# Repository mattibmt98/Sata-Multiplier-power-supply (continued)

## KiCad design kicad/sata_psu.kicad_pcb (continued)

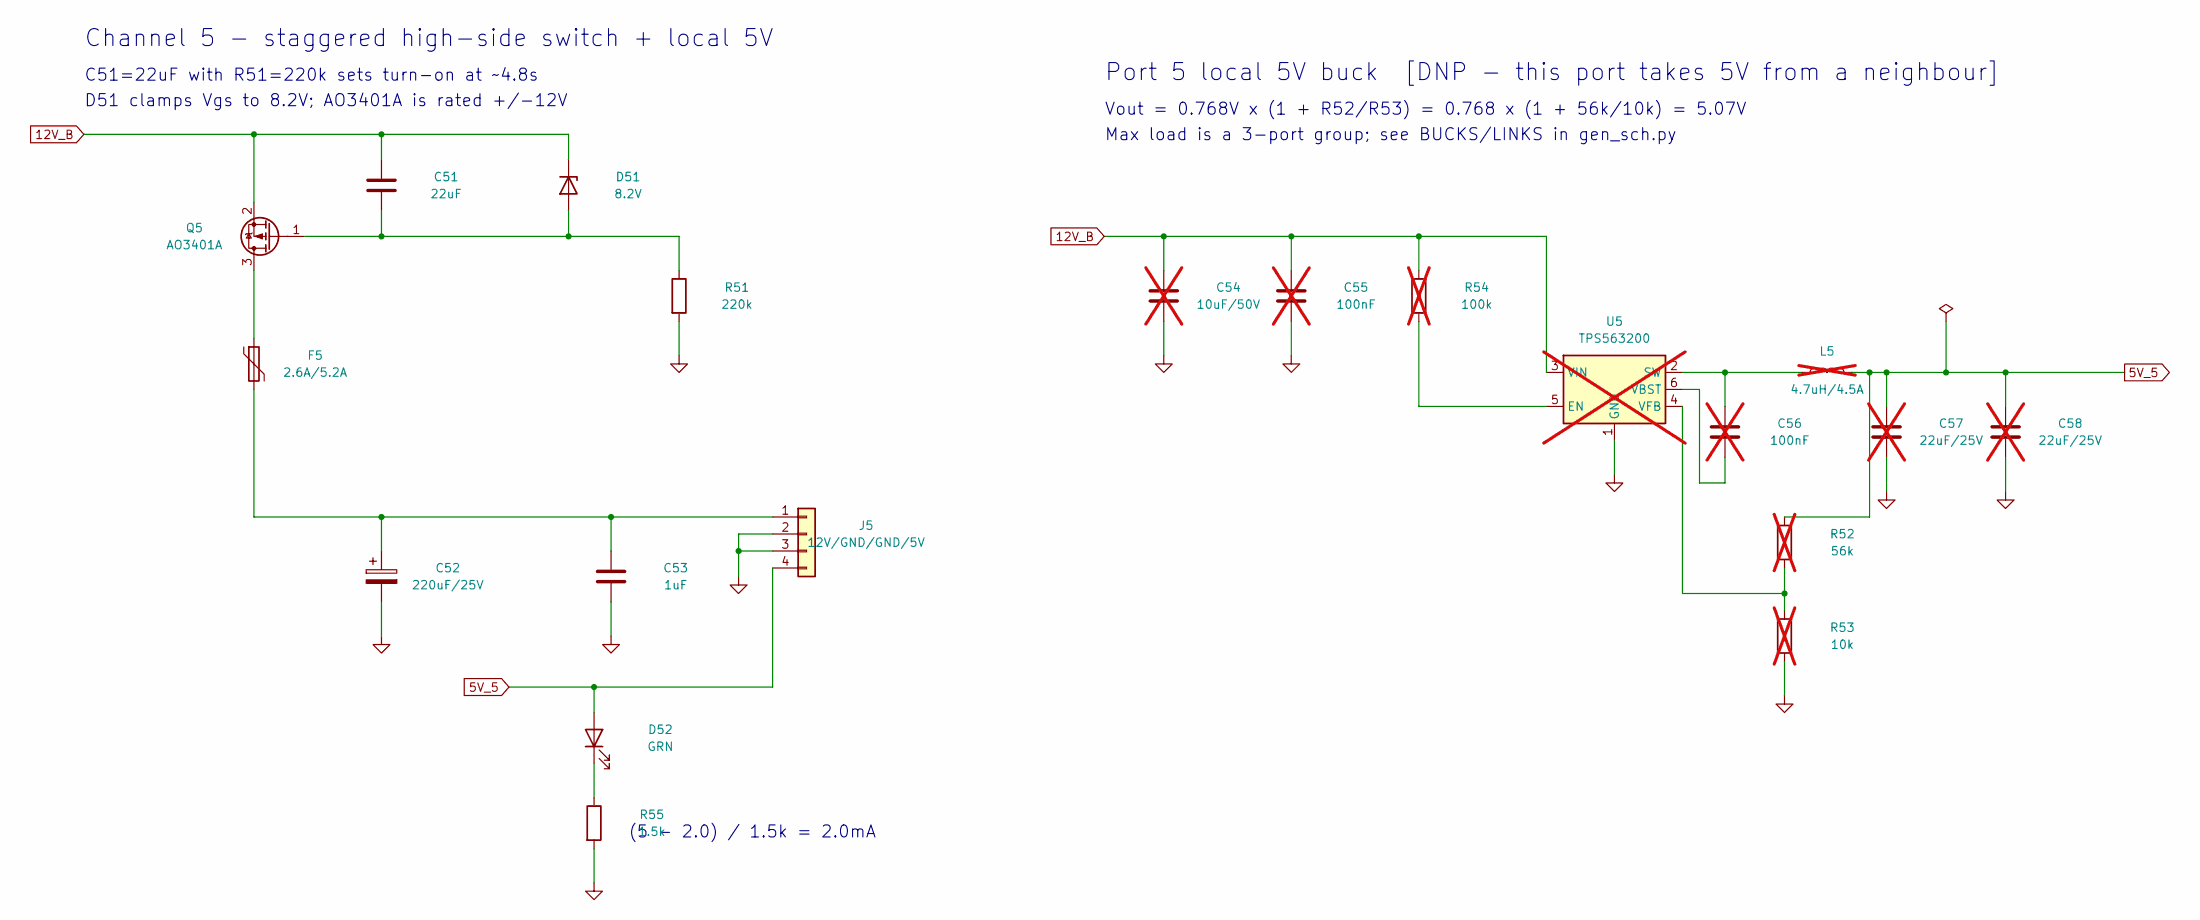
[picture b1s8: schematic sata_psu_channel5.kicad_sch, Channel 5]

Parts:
C51: 22uF; C_1206_3216Metric; MPN CL31A226KAHNNNE; DigiKey 1276-3047-1-ND
C52: 220uF/25V; CP_Radial_D8.0mm_P3.50mm; MPN UVZ1E221MPD; DigiKey 493-1302-ND
C53: 1uF; C_0603_1608Metric; MPN CL10A105KB8NNNC; DigiKey 1276-1860-1-ND
C54: 10uF/50V; C_1206_3216Metric; MPN CL31A106KBHNNNE; DigiKey 1276-2876-1-ND; not fitted
C55, C56: 100nF; C_0603_1608Metric; MPN CL10B104KB8NNNC; DigiKey 1276-1000-1-ND; not fitted
C57, C58: 22uF/25V; C_1206_3216Metric; MPN CL31A226KAHNNNE; DigiKey 1276-3047-1-ND; not fitted
D51: 8.2V; D_SOD-123; MPN MMSZ5237B-7-F; DigiKey MMSZ5237B-FDICT-ND
D52: GRN; LED_0603_1608Metric
F5: 2.6A/5.2A; Fuse_1812_4532Metric; MPN 1812L260/16MR; DigiKey F10827CT-ND
J5: 12V/GND/GND/5V; PinHeader_1x04_P2.54mm_Vertical; MPN PRPC004SAAN-RC; DigiKey S1011EC-04-ND
L5: 4.7uH/4.5A; L_Bourns_SRN6045TA; MPN SRN6045TA-4R7M; DigiKey SRN6045TA-4R7MTR-ND; not fitted
Q5: AO3401A; SOT-23; MPN AO3401A; DigiKey 785-1001-1-ND
R51: 220k; R_0603_1608Metric; MPN RC0603FR-07220KL; DigiKey 311-220KHRCT-ND
R52: 56k; R_0603_1608Metric; MPN RC0603FR-0756KL; DigiKey 311-56KHRCT-ND; not fitted
R53: 10k; R_0603_1608Metric; MPN RC0603FR-0710KL; DigiKey 311-10.0KHRCT-ND; not fitted
R54: 100k; R_0603_1608Metric; MPN RC0603FR-07100KL; DigiKey 311-100KHRCT-ND; not fitted
R55: 1.5k; R_0603_1608Metric
U5: TPS563200; SOT-23-6; MPN TPS563200DDCR; DigiKey 296-43663-1-ND; not fitted

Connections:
5V_5: C57.1, C58.1, D52.2 (A), J5.4, L5.2, R52.1; also elsewhere on the board
12V_B: C51.1, C54.1, C55.1, D51.1 (K), Q5.2 (S), R54.1, U5.3 (VIN); also elsewhere on the board
GND: C52.2, C53.2, C54.2, C55.2, C57.2, C58.2, J5.2, J5.3, R51.2, R53.2, R55.2, U5.1 (GND); also elsewhere on the board
unnamed: C51.2, D51.2 (A), Q5.1 (G), R51.1
unnamed: D52.1 (K), R55.1
unnamed: C52.1, C53.1, F5.2, J5.1
unnamed: F5.1, Q5.3 (D)
unnamed: R54.2, U5.5 (EN)
unnamed: C56.1, L5.1, U5.2 (SW)
unnamed: C56.2, U5.6 (VBST)
unnamed: R52.2, R53.1, U5.4 (VFB)

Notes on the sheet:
Channel 5 - staggered high-side switch + local 5V
C51=22uF with R51=220k sets turn-on at ~4.8s
D51 clamps Vgs to 8.2V; AO3401A is rated +/-12V
(5 - 2.0) / 1.5k = 2.0mA
Port 5 local 5V buck [DNP - this port takes 5V from a neighbour]
Vout = 0.768V x (1 + R52/R53) = 0.768 x (1 + 56k/10k) = 5.07V
Max load is a 3-port group; see BUCKS/LINKS in gen_sch.py

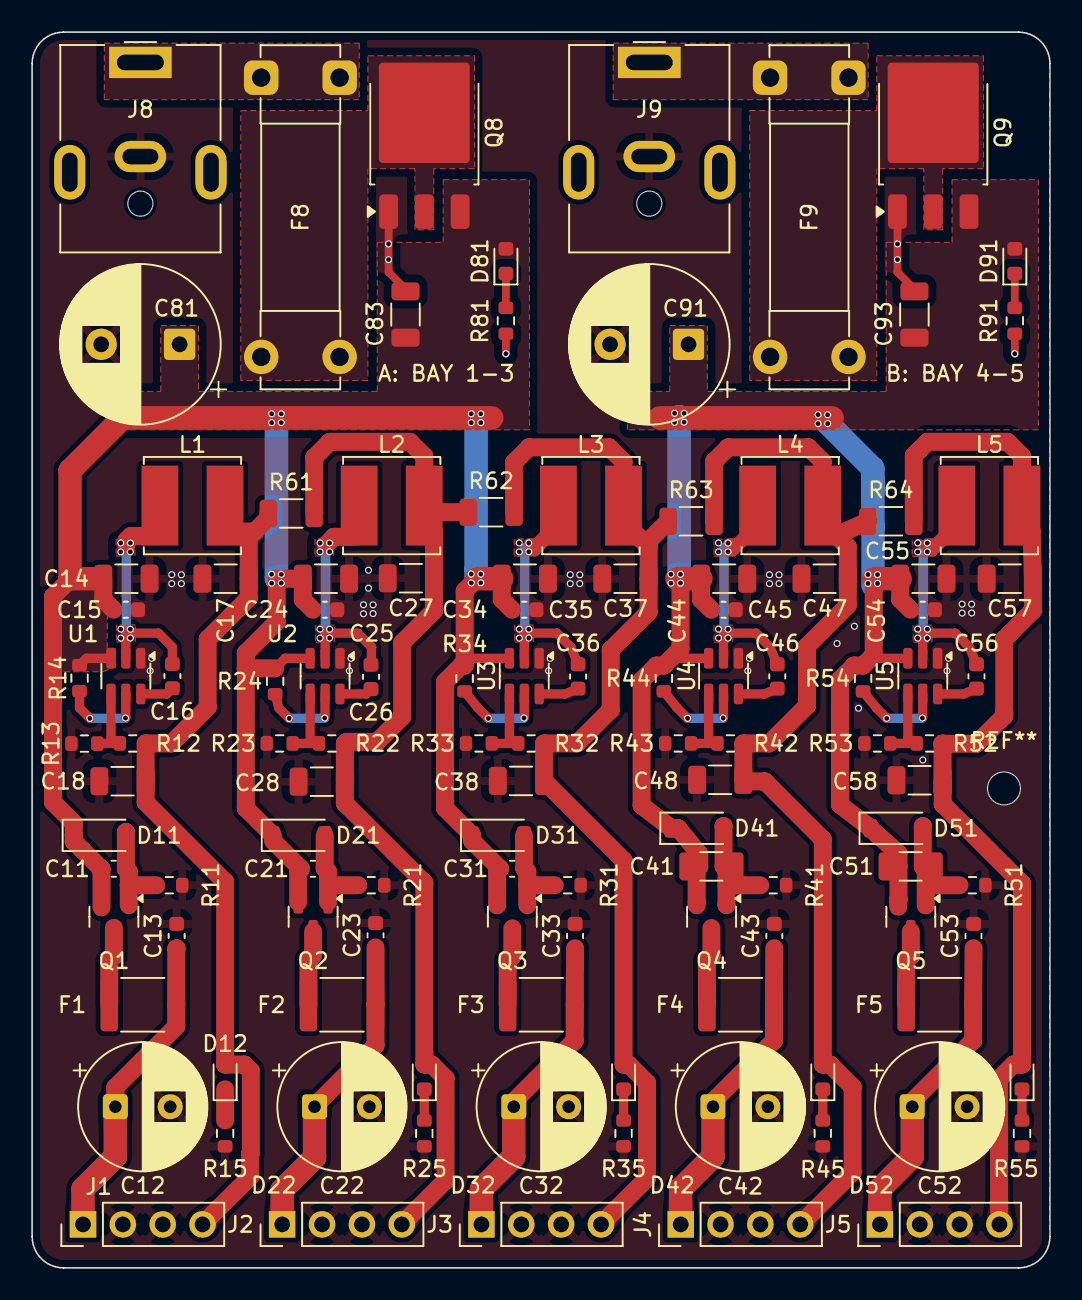
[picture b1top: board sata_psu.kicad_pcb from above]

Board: 2 copper layers, 64.9 x 78.8 mm, 118 parts (0 on the bottom side), 54 nets.

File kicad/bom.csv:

"Reference","Value","Footprint","MPN","DigiKey","DNP"
"C11,C13,C23,C33,C43,C53","1uF","Capacitor_SMD:C_0603_1608Metric","CL10A105KB8NNNC","1276-1860-1-ND",""
"C12,C22,C32,C42,C52","220uF/25V","Capacitor_THT:CP_Radial_D8.0mm_P3.50mm","UVZ1E221MPD","493-1302-ND",""
"C14,C34,C54","10uF/50V","Capacitor_SMD:C_1206_3216Metric","CL31A106KBHNNNE","1276-2876-1-ND","DNP"
"C15,C16,C35,C36,C55,C56","100nF","Capacitor_SMD:C_0603_1608Metric","CL10B104KB8NNNC","1276-1000-1-ND","DNP"
"C17,C18,C37,C38,C57,C58","22uF/25V","Capacitor_SMD:C_1206_3216Metric","CL31A226KAHNNNE","1276-3047-1-ND","DNP"
"C21","2.2uF","Capacitor_SMD:C_0603_1608Metric","CL10A225KO8NNNC","1276-1040-1-ND",""
"C24,C44,C83,C93","10uF/50V","Capacitor_SMD:C_1206_3216Metric","CL31A106KBHNNNE","1276-2876-1-ND",""
"C25,C26,C45,C46","100nF","Capacitor_SMD:C_0603_1608Metric","CL10B104KB8NNNC","1276-1000-1-ND",""
"C27,C28,C47,C48","22uF/25V","Capacitor_SMD:C_1206_3216Metric","CL31A226KAHNNNE","1276-3047-1-ND",""
"C31","4.7uF","Capacitor_SMD:C_0603_1608Metric","CL10A475KO8NNNC","1276-1784-1-ND",""
"C41","10uF","Capacitor_SMD:C_1206_3216Metric","CL31A106KBHNNNE","1276-2876-1-ND",""
"C51","22uF","Capacitor_SMD:C_1206_3216Metric","CL31A226KAHNNNE","1276-3047-1-ND",""
"C81,C91","1000uF/25V","Capacitor_THT:CP_Radial_D10.0mm_P5.00mm","UVR1E102MPD","493-1065-ND",""
"D11,D21,D31,D41,D51","8.2V","Diode_SMD:D_SOD-123","MMSZ5237B-7-F","MMSZ5237B-FDICT-ND",""
"D12,D22,D32,D42,D52,D81,D91","GRN","LED_SMD:LED_0603_1608Metric","","",""
"F1-F5","2.6A/5.2A","Fuse:Fuse_1812_4532Metric","1812L260/16MR","F10827CT-ND",""
"F8,F9","8A fast-blow","Fuse:Fuseholder_Clip-5x20mm_Bel_FC-203-22_Lateral_P17.80x5.00mm_D1.17mm_Horizontal","FC-203-22","507-1703-ND",""
"J1-J5","12V/GND/GND/5V","Connector_PinHeader_2.54mm:PinHeader_1x04_P2.54mm_Vertical","PRPC004SAAN-RC","S1011EC-04-ND",""
"J8,J9","12V DC 5-8A","Connector_BarrelJack:BarrelJack_CUI_PJ-063AH_Horizontal","PJ-063AH","CP-063AH-ND",""
"L1,L3,L5","4.7uH/4.5A","Inductor_SMD:L_Bourns_SRN6045TA","SRN6045TA-4R7M","SRN6045TA-4R7MTR-ND","DNP"
"L2,L4","4.7uH/4.5A","Inductor_SMD:L_Bourns_SRN6045TA","SRN6045TA-4R7M","SRN6045TA-4R7MTR-ND",""
"Q1-Q5","AO3401A","Package_TO_SOT_SMD:SOT-23","AO3401A","785-1001-1-ND",""
"Q8,Q9","AOD4185","Package_TO_SOT_SMD:TO-252-3_TabPin2","AOD4185","785-1222-2-ND",""
"R11,R21,R31,R41,R51","220k","Resistor_SMD:R_0603_1608Metric","RC0603FR-07220KL","311-220KHRCT-ND",""
"R12,R32,R52","56k","Resistor_SMD:R_0603_1608Metric","RC0603FR-0756KL","311-56KHRCT-ND","DNP"
"R13,R33,R53","10k","Resistor_SMD:R_0603_1608Metric","RC0603FR-0710KL","311-10.0KHRCT-ND","DNP"
"R14,R34,R54","100k","Resistor_SMD:R_0603_1608Metric","RC0603FR-07100KL","311-100KHRCT-ND","DNP"
"R15,R25,R35,R45,R55","1.5k","Resistor_SMD:R_0603_1608Metric","","",""
"R22,R42","56k","Resistor_SMD:R_0603_1608Metric","RC0603FR-0756KL","311-56KHRCT-ND",""
"R23,R43","10k","Resistor_SMD:R_0603_1608Metric","RC0603FR-0710KL","311-10.0KHRCT-ND",""
"R24,R44","100k","Resistor_SMD:R_0603_1608Metric","RC0603FR-07100KL","311-100KHRCT-ND",""
"R61,R62,R64","0R","Resistor_SMD:R_1206_3216Metric","","",""
"R63","0R","Resistor_SMD:R_1206_3216Metric","","","DNP"
"R81,R91","4.7k","Resistor_SMD:R_0603_1608Metric","","",""
"U1,U3,U5","TPS563200","Package_TO_SOT_SMD:SOT-23-6","TPS563200DDCR","296-43663-1-ND","DNP"
"U2,U4","TPS563200","Package_TO_SOT_SMD:SOT-23-6","TPS563200DDCR","296-43663-1-ND",""
